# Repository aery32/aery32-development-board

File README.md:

Aery32 Development Board
========================

<br /><span xmlns:dct="http://purl.org/dc/terms/" property="dct:title">Aery32 Development Board</span> by <a xmlns:cc="http://creativecommons.org/ns#" href="www.muiku.com" property="cc:attributionName" rel="cc:attributionURL">Muiku Oy</a> is licensed under a <a rel="license" href="http://creativecommons.org/licenses/by-sa/3.0/">Creative Commons Attribution-ShareAlike 3.0 Unported License</a>.<br />Permissions beyond the scope of this license may be available at <a xmlns:cc="http://creativecommons.org/ns#" href="www.muiku.com" rel="cc:morePermissions">www.muiku.com</a>.

Copyright (c) 2012, Muiku Oy
All rights reserved.

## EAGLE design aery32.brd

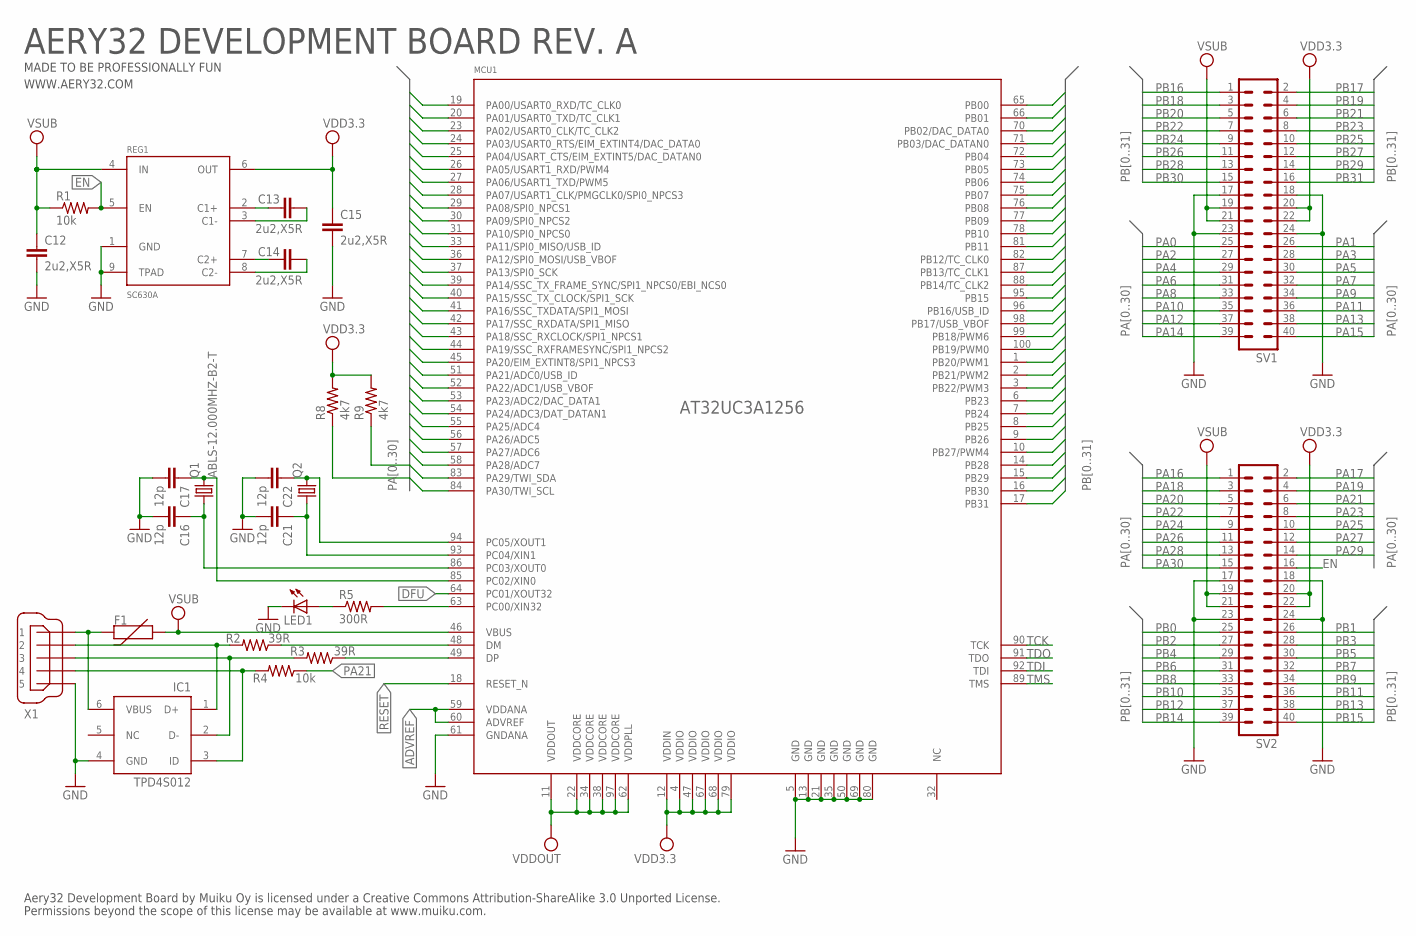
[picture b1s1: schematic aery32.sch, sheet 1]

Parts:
C12, C13, C14, C15: 2u2,X5R; C0402
C16, C17, C21, C22: 12p; C0402
F1: PTCSMD; PTC-1206
IC1: TPD4S012; DRY
LED1: LEDCHIPLED_0805; CHIPLED_0805
MCU1: AT32UC3A1256; TQFP100; DIGIKEY AT32UC3A1256-AUT-ND
Q1: ABLS-12.000MHZ-B2-T; HC49UP; DIGIKEY 535-9067-1-ND
Q2: CRYSTALTC38H; TC38H
R1, R4: 10k; R0402
R2, R3: 39R; R0402
R5: 300R; R0402
R8, R9: 4k7; R0402
REG1: SC630A; MLPD-UT-8
SV1, SV2: MA20-2
X1: USBMINI-B; MINIUSB

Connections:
ADVREF: MCU1.59 (VDDANA), MCU1.60 (ADVREF); also elsewhere on the board
DFU: MCU1.64 (PC01/XOUT32); also elsewhere on the board
EN: R1.2, REG1.5 (EN), SV2.16
GND: C12.2, C15.2, C16.2, C17.2, C21.2, C22.2, IC1.4 (GND), LED1.C, MCU1.5 (GND), MCU1.13 (GND), MCU1.21 (GND), MCU1.35 (GND), MCU1.50 (GND), MCU1.61 (GNDANA), MCU1.69 (GND), MCU1.80 (GND), REG1.1 (GND), REG1.9 (TPAD), SV1.17, SV1.18, SV1.23, SV1.24, SV2.17, SV2.18, SV2.23, SV2.24, X1.5; also elsewhere on the board
unnamed: C13.1, REG1.2 (C1+)
unnamed: MCU1.63 (PC00/XIN32), R5.2
unnamed: IC1.3 (ID), R4.2, X1.4
unnamed: MCU1.48 (DM), R2.1
unnamed: MCU1.49 (DP), R3.1
unnamed: IC1.2 (D-), R3.2, X1.3
unnamed: IC1.1 (D+), R2.2, X1.2
unnamed: LED1.A, R5.1
unnamed: F1.2, IC1.6 (VBUS), X1.1
unnamed: C13.2, REG1.3 (C1-)
unnamed: C14.1, REG1.7 (C2+)
unnamed: C14.2, REG1.8 (C2-)
unnamed: C16.1, MCU1.86 (PC03/XOUT0), Q1.1
unnamed: C22.1, MCU1.94 (PC05/XOUT1), Q2.2
unnamed: C17.1, MCU1.85 (PC02/XIN0), Q1.2
unnamed: C21.1, MCU1.93 (PC04/XIN1), Q2.1
PA0: MCU1.19 (PA00/USART0_RXD/TC_CLK0), SV1.25
PA1: MCU1.20 (PA01/USART0_TXD/TC_CLK1), SV1.26
PA2: MCU1.23 (PA02/USART0_CLK/TC_CLK2), SV1.27
PA3: MCU1.24 (PA03/USART0_RTS/EIM_EXTINT4/DAC_DATA0), SV1.28
PA4: MCU1.25 (PA04/USART_CTS/EIM_EXTINT5/DAC_DATAN0), SV1.29
PA5: MCU1.26 (PA05/USART1_RXD/PWM4), SV1.30
PA6: MCU1.27 (PA06/USART1_TXD/PWM5), SV1.31
PA7: MCU1.28 (PA07/USART1_CLK/PMGCLK0/SPI0_NPCS3), SV1.32
PA8: MCU1.29 (PA08/SPI0_NPCS1), SV1.33
PA9: MCU1.30 (PA09/SPI0_NPCS2), SV1.34
PA10: MCU1.31 (PA10/SPI0_NPCS0), SV1.35
PA11: MCU1.33 (PA11/SPI0_MISO/USB_ID), SV1.36
PA12: MCU1.36 (PA12/SPI0_MOSI/USB_VBOF), SV1.37
PA13: MCU1.37 (PA13/SPI0_SCK), SV1.38
PA14: MCU1.39 (PA14/SSC_TX_FRAME_SYNC/SPI1_NPCS0/EBI_N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), SV1.39
PA15: MCU1.40 (PA15/SSC_TX_CLOCK/SPI1_SCK), SV1.40
PA16: MCU1.41 (PA16/SSC_TXDATA/SPI1_MOSI), SV2.1
PA17: MCU1.42 (PA17/SSC_RXDATA/SPI1_MISO), SV2.2
PA18: MCU1.43 (PA18/SSC_RXCLOCK/SPI1_NPCS1), SV2.3
PA19: MCU1.44 (PA19/SSC_RXFRAMESYNC/SPI1_NPCS2), SV2.4
PA20: MCU1.45 (PA20/EIM_EXTINT8/SPI1_NPCS3), SV2.5
PA21: MCU1.51 (PA21/ADC0/USB_ID), R4.1, SV2.6
PA22: MCU1.52 (PA22/ADC1/USB_VBOF), SV2.7
PA23: MCU1.53 (PA23/ADC2/DAC_DATA1), SV2.8
PA24: MCU1.54 (PA24/ADC3/DAT_DATAN1), SV2.9
PA25: MCU1.55 (PA25/ADC4), SV2.10
PA26: MCU1.56 (PA26/ADC5), SV2.11
PA27: MCU1.57 (PA27/ADC6), SV2.12
PA28: MCU1.58 (PA28/ADC7), SV2.13
PA29: MCU1.83 (PA29/TWI_SDA), R9.1, SV2.14
PA30: MCU1.84 (PA30/TWI_SCL), R8.1, SV2.15
PB0: MCU1.65 (PB00), SV2.25
PB1: MCU1.66 (PB01), SV2.26
PB2: MCU1.70 (PB02/DAC_DATA0), SV2.27
PB3: MCU1.71 (PB03/DAC_DATAN0), SV2.28
PB4: MCU1.72 (PB04), SV2.29
PB5: MCU1.73 (PB05), SV2.30
PB6: MCU1.74 (PB06), SV2.31
PB7: MCU1.75 (PB07), SV2.32
PB8: MCU1.76 (PB08), SV2.33
PB9: MCU1.77 (PB09), SV2.34
PB10: MCU1.78 (PB10), SV2.35
PB11: MCU1.81 (PB11), SV2.36
PB12: MCU1.82 (PB12/TC_CLK0), SV2.37
PB13: MCU1.87 (PB13/TC_CLK1), SV2.38
PB14: MCU1.88 (PB14/TC_CLK2), SV2.39
PB15: MCU1.95 (PB15), SV2.40
PB16: MCU1.96 (PB16/USB_ID), SV1.1
PB17: MCU1.98 (PB17/USB_VBOF), SV1.2
PB18: MCU1.99 (PB18/PWM6), SV1.3
PB19: MCU1.100 (PB19/PWM0), SV1.4
PB20: MCU1.1 (PB20/PWM1), SV1.5
PB21: MCU1.2 (PB21/PWM2), SV1.6
PB22: MCU1.3 (PB22/PWM3), SV1.7
PB23: MCU1.6 (PB23), SV1.8
PB24: MCU1.7 (PB24), SV1.9
PB25: MCU1.8 (PB25), SV1.10
PB26: MCU1.9 (PB26), SV1.11
PB27: MCU1.10 (PB27/PWM4), SV1.12
PB28: MCU1.14 (PB28), SV1.13
PB29: MCU1.15 (PB29), SV1.14
PB30: MCU1.16 (PB30), SV1.15
PB31: MCU1.17 (PB31), SV1.16
RESET: MCU1.18 (RESET_N); also elsewhere on the board
TCK: MCU1.90 (TCK); also elsewhere on the board
TDI: MCU1.92 (TDI); also elsewhere on the board
TDO: MCU1.91 (TDO); also elsewhere on the board
TMS: MCU1.89 (TMS); also elsewhere on the board
VBUS: C12.1, F1.1, MCU1.46 (VBUS), R1.1, REG1.4 (IN), SV1.19, SV1.21, SV2.19, SV2.21
VDD3.3: C15.1, MCU1.4 (VDDIO), MCU1.12 (VDDIN), MCU1.47 (VDDIO), MCU1.67 (VDDIO), MCU1.68 (VDDIO), MCU1.79 (VDDIO), R8.2, R9.2, REG1.6 (OUT), SV1.20, SV1.22, SV2.20, SV2.22; also elsewhere on the board
VDDOUT: MCU1.11 (VDDOUT), MCU1.22 (VDDCORE), MCU1.34 (VDDCORE), MCU1.38 (VDDCORE), MCU1.62 (VDDPLL), MCU1.97 (VDDCORE); also elsewhere on the board

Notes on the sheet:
Aery32 Development Board by Muiku Oy is licensed under a Creative Commons Attribution-ShareAlike 3.0 Unported License.
Permissions beyond the scope of this license may be available at www.muiku.com.
AERY32 DEVELOPMENT BOARD REV. A
MADE TO BE PROFESSIONALLY FUN
WWW.AERY32.COM

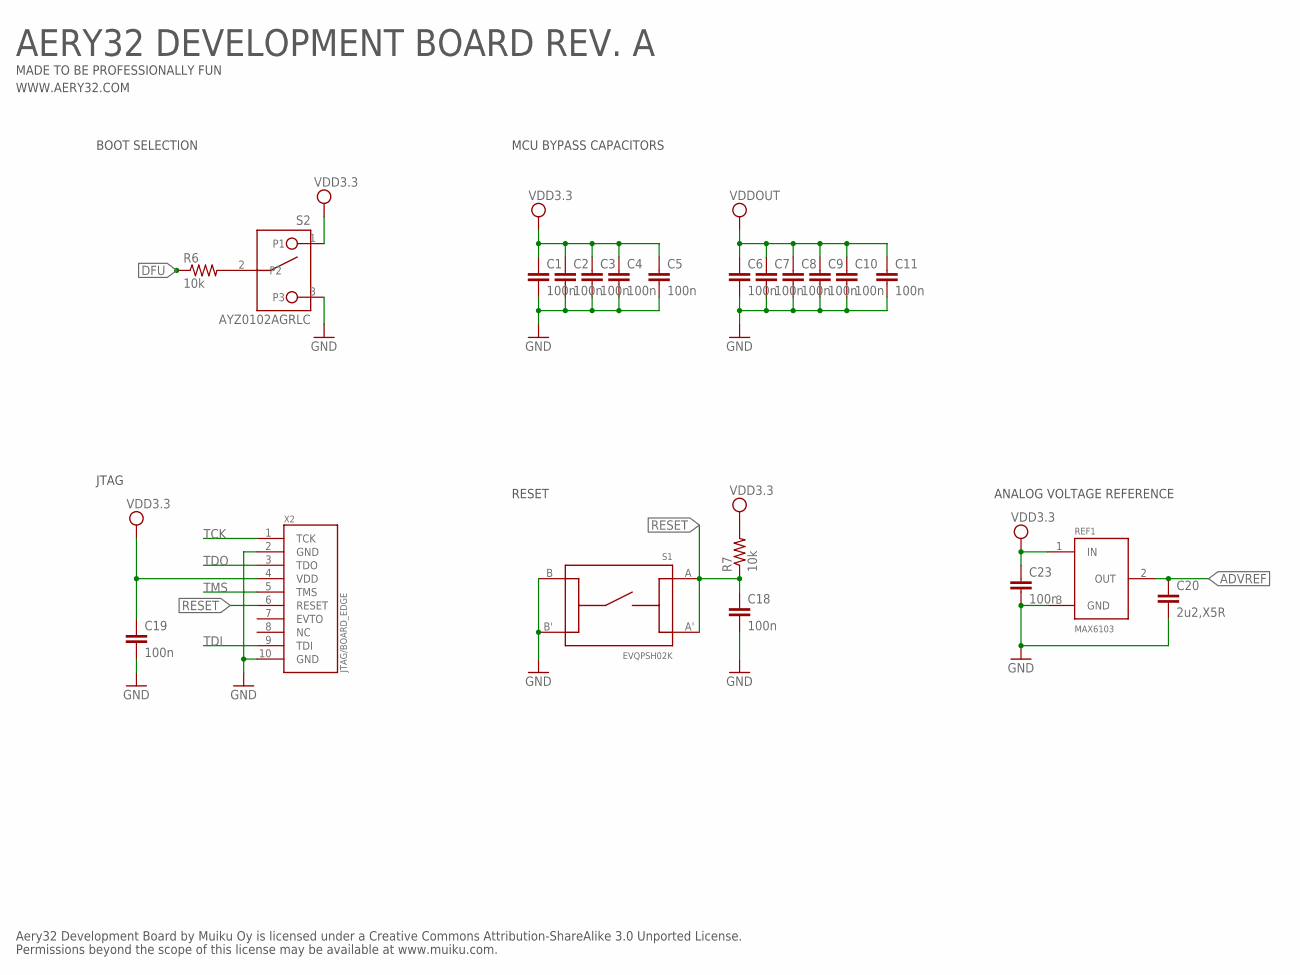
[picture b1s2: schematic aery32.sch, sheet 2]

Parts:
C1, C2, C3, C4, C5, C6, C7, C8, C9, C10, C11, C18, C19, C23: 100n; C0402
C20: 2u2,X5R; C0402
R6, R7: 10k; R0402
REF1: MAX6103; SOT23
S1: EVQPSH02K
S2: AYZ0102AGRLC
X2: JTAG/BOARD_EDGE

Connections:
ADVREF: C20.1, REF1.2 (OUT); also elsewhere on the board
DFU: R6.1; also elsewhere on the board
GND: C1.2, C2.2, C3.2, C4.2, C5.2, C6.2, C7.2, C8.2, C9.2, C10.2, C11.2, C18.2, C19.2, C20.2, C23.2, REF1.3 (GND), S1.B, S1.B', S2.3, X2.2 (GND), X2.10 (GND); also elsewhere on the board
unnamed: R6.2, S2.2
RESET: C18.1, R7.1, S1.A, S1.A', X2.6 (RESET); also elsewhere on the board
TCK: X2.1 (TCK); also elsewhere on the board
TDI: X2.9 (TDI); also elsewhere on the board
TDO: X2.3 (TDO); also elsewhere on the board
TMS: X2.5 (TMS); also elsewhere on the board
VDD3.3: C1.1, C2.1, C3.1, C4.1, C5.1, C19.1, C23.1, R7.2, REF1.1 (IN), S2.1, X2.4 (VDD); also elsewhere on the board
VDDOUT: C6.1, C7.1, C8.1, C9.1, C10.1, C11.1; also elsewhere on the board

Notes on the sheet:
MCU BYPASS CAPACITORS
ANALOG VOLTAGE REFERENCE
BOOT SELECTION
JTAG
RESET
Aery32 Development Board by Muiku Oy is licensed under a Creative Commons Attribution-ShareAlike 3.0 Unported License.
Permissions beyond the scope of this license may be available at www.muiku.com.
AERY32 DEVELOPMENT BOARD REV. A
MADE TO BE PROFESSIONALLY FUN
WWW.AERY32.COM

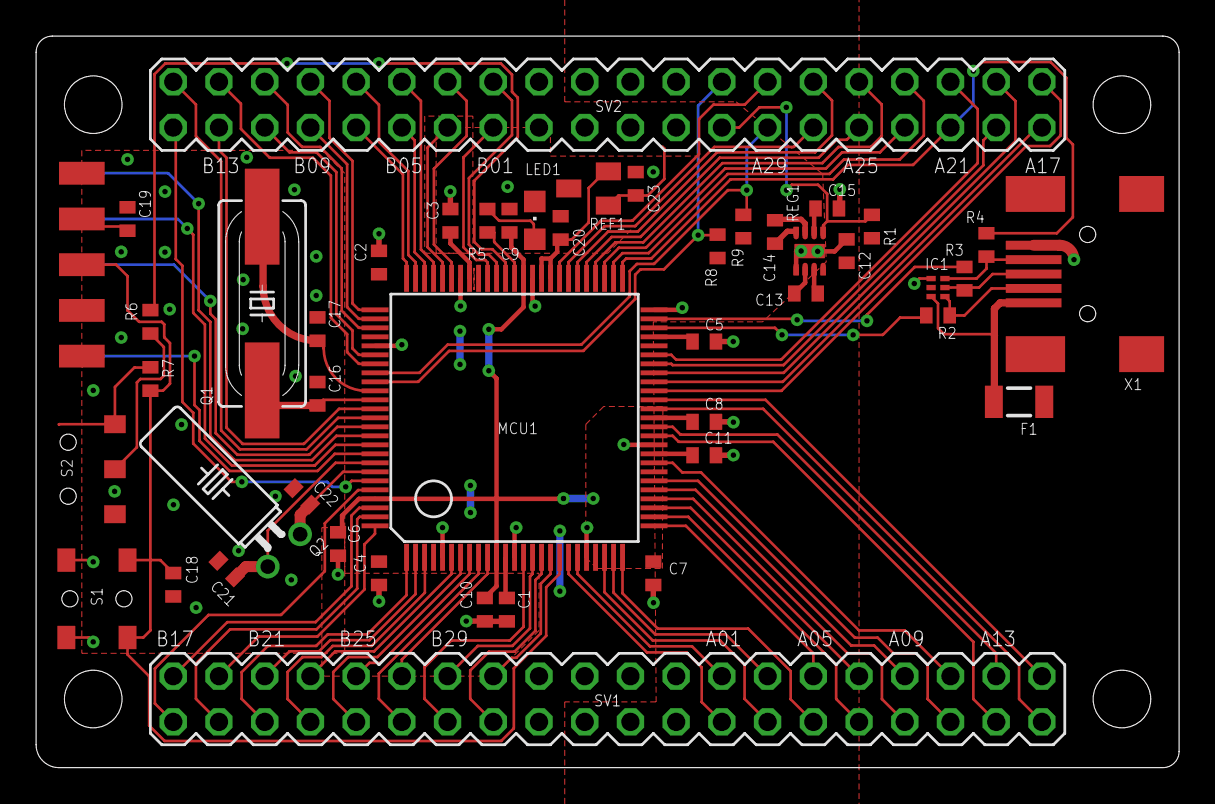
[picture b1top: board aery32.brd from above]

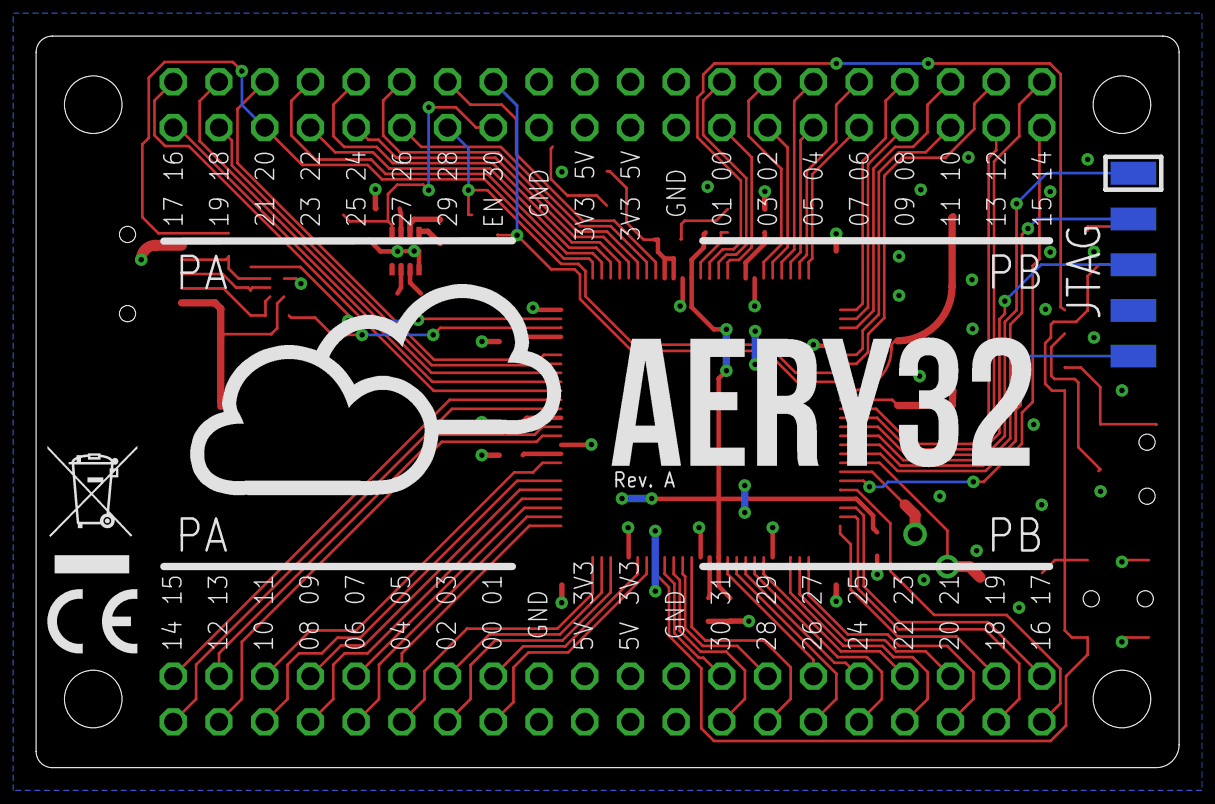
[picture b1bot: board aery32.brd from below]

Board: 2 copper layers, 63.5 x 40.6 mm, 49 parts (4 on the bottom side), 92 nets.

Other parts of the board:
U$16: CE/5MM-WIDE
U$18: WEEE/5MM-WIDE
U$19: LOGO/AERY32

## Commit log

2013-04-14 Revision A
